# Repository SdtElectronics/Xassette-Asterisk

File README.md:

# Xassette-Asterisk
Evaluation board for AllWinner's RISC-V 64 SoC F133/D1s

## Highlights
* Breaks out all IOs, involving analog peripherals, in a compact 56*56mm 2-layer board
* Comes with standard interfaces including USB, micro SD, LCD, Line-in and headphone
* Optimized components arrangement for soldering on a hot plate

## About the Chip
D1s/F133: RISC-V 64 single core @1.008G with in package 64MB DDR2

## Guides
[Quick Start](docs/quickStart.md)

[Troubleshooting](docs/troubleshooting.md)

[Wi-Fi](docs/WiFi.md)

## Pin Out

Pins for LCD and DVP camera can also be used as IOs. See schematic below for detailed pin assignment.

## Schematic & BOM

The schematic in KiCAD format is available under [hw](hw/). BOM in csv format is at [docs/BOM.csv](docs/BOM.csv), and kitspace provides an [online BOM](https://kitspace.org/interactive_bom/?github.com/SdtElectronics/Xassette-Asterisk). Do note that many components are optional (required by some specific peripherals)!

## Notes
* Leave all BOOT selection resistors unconnected if only one BOOT media is present
* Choose load capacitors according to specs of crystals
* When board is to be powered by 3.3V, connect to the power via the 3.3V pin of the pinheader, and `D4` should be soldered. Note USB host will not work properly in this condition due to the absence of 5V power.

## Accessories
### IO Expansion Board
To make use of IOs in the LCD port easier, [this expansion board](hw/auxiliary/Brk40p) converts all nets from FPC to 2.54mm pin headers with labeled IO indices. For 24pin DVP port, there is also an [expansion board](https://github.com/SdtElectronics/Biscuits/tree/master/24P_FPC_FFC_Breakout) but with no labels.

## CHANGELOG
### hw-v0.2 
* Added WiFi Module on `sdc2`, sharing pins with SPI Flash
* Added FEL button
* Added ESD protection on USB and audio jacks
* Changed pin headers of TVIN and FMIN (`J10`) to 2x3 2.00mm to optimize routing of USB

### fw-v0.2
* Enabled pins of `sdc2` for SDIO
* Packed driver for RTL8189ftv WiFi module

**NOTE**: hw-v0.1 board can **NOT** boot fw-v0.2 firmware. Use fw-v0.1 instead.

### hw-v0.3
* Fix pull-up/down resistors for USB-PD role detection
* Align voltage of `VDDIO` in DVP interface with `VCC-PE`

## FAQ
> Are you going to sell some manufactured boards?

No. I have no time and resource to batch manufacture this board. Some commercial boards should come in a couple of months (not from me).

> Where to buy some D1s chips?

There are several suppliers providing samples on taobao.

> Where to find the BSP? Can I build the firmware myself?

The tina BSP for D1s is opened to public and you can download it via [the mirror at linux-sunxi.org](https://dl.linux-sunxi.org/D1/SDK/). There is also [a good guide on linux-sunxi.org](https://linux-sunxi.org/D1_SDK_Howto) covering the building and trouble shooting.

> More information? Like what can this board do now?

The progress of this project is logged at [this Hackaday page](https://hackaday.io/project/182389-the-cheapest-risc-v-64-computer-by-now), and this repository will contain the source and documentation of this board only. Currently this board can boot up the tina Linux system (an OpenWRT fork by Allwinner) and populate a shell prompt via the serial, drive a parallel RGB display, play sounds via the headphone socket, and record audio from MIC. More functionalities will be tested in the future.

**Additional Words**

This project has gained unexpected popularity since the announcement. Thanks for all the interest! However, I am merely an enthusiast with limited time can be put on this, so I am sorry to disappoint who want to buy one. It is perfectly Okay if someone want to put this into production, as long as my work is acknowledged and the Licence is followed (better if you could contact me in advance). 

D1s is an awesome chip with many features to be exploited. Designing a PCB is not hard as the arrangement of pins is quite thoughtful. The crucial part is correct values of some key components, and they were all marked in the schematic. A symbol of D1s with annotated pins is also included in this repository, so this should also be a good start point for your own design.

## External Links
[Page on Hackaday ](https://hackaday.io/project/182389-the-cheapest-risc-v-64-computer-by-now)

[Post about batch manufacturing by cnx-software](https://www.cnx-software.com/2021/12/24/manufacturing-xassette-asterisk-open-source-hardware-board/)

[WiKi on Linux-sunxi.org](https://linux-sunxi.org/Xassette_Asterisk)

## Licence
This project is available under the [CERN OHL-w v2](https://ohwr.org/project/cernohl/wikis/Documents/CERN-OHL-version-2) licence.

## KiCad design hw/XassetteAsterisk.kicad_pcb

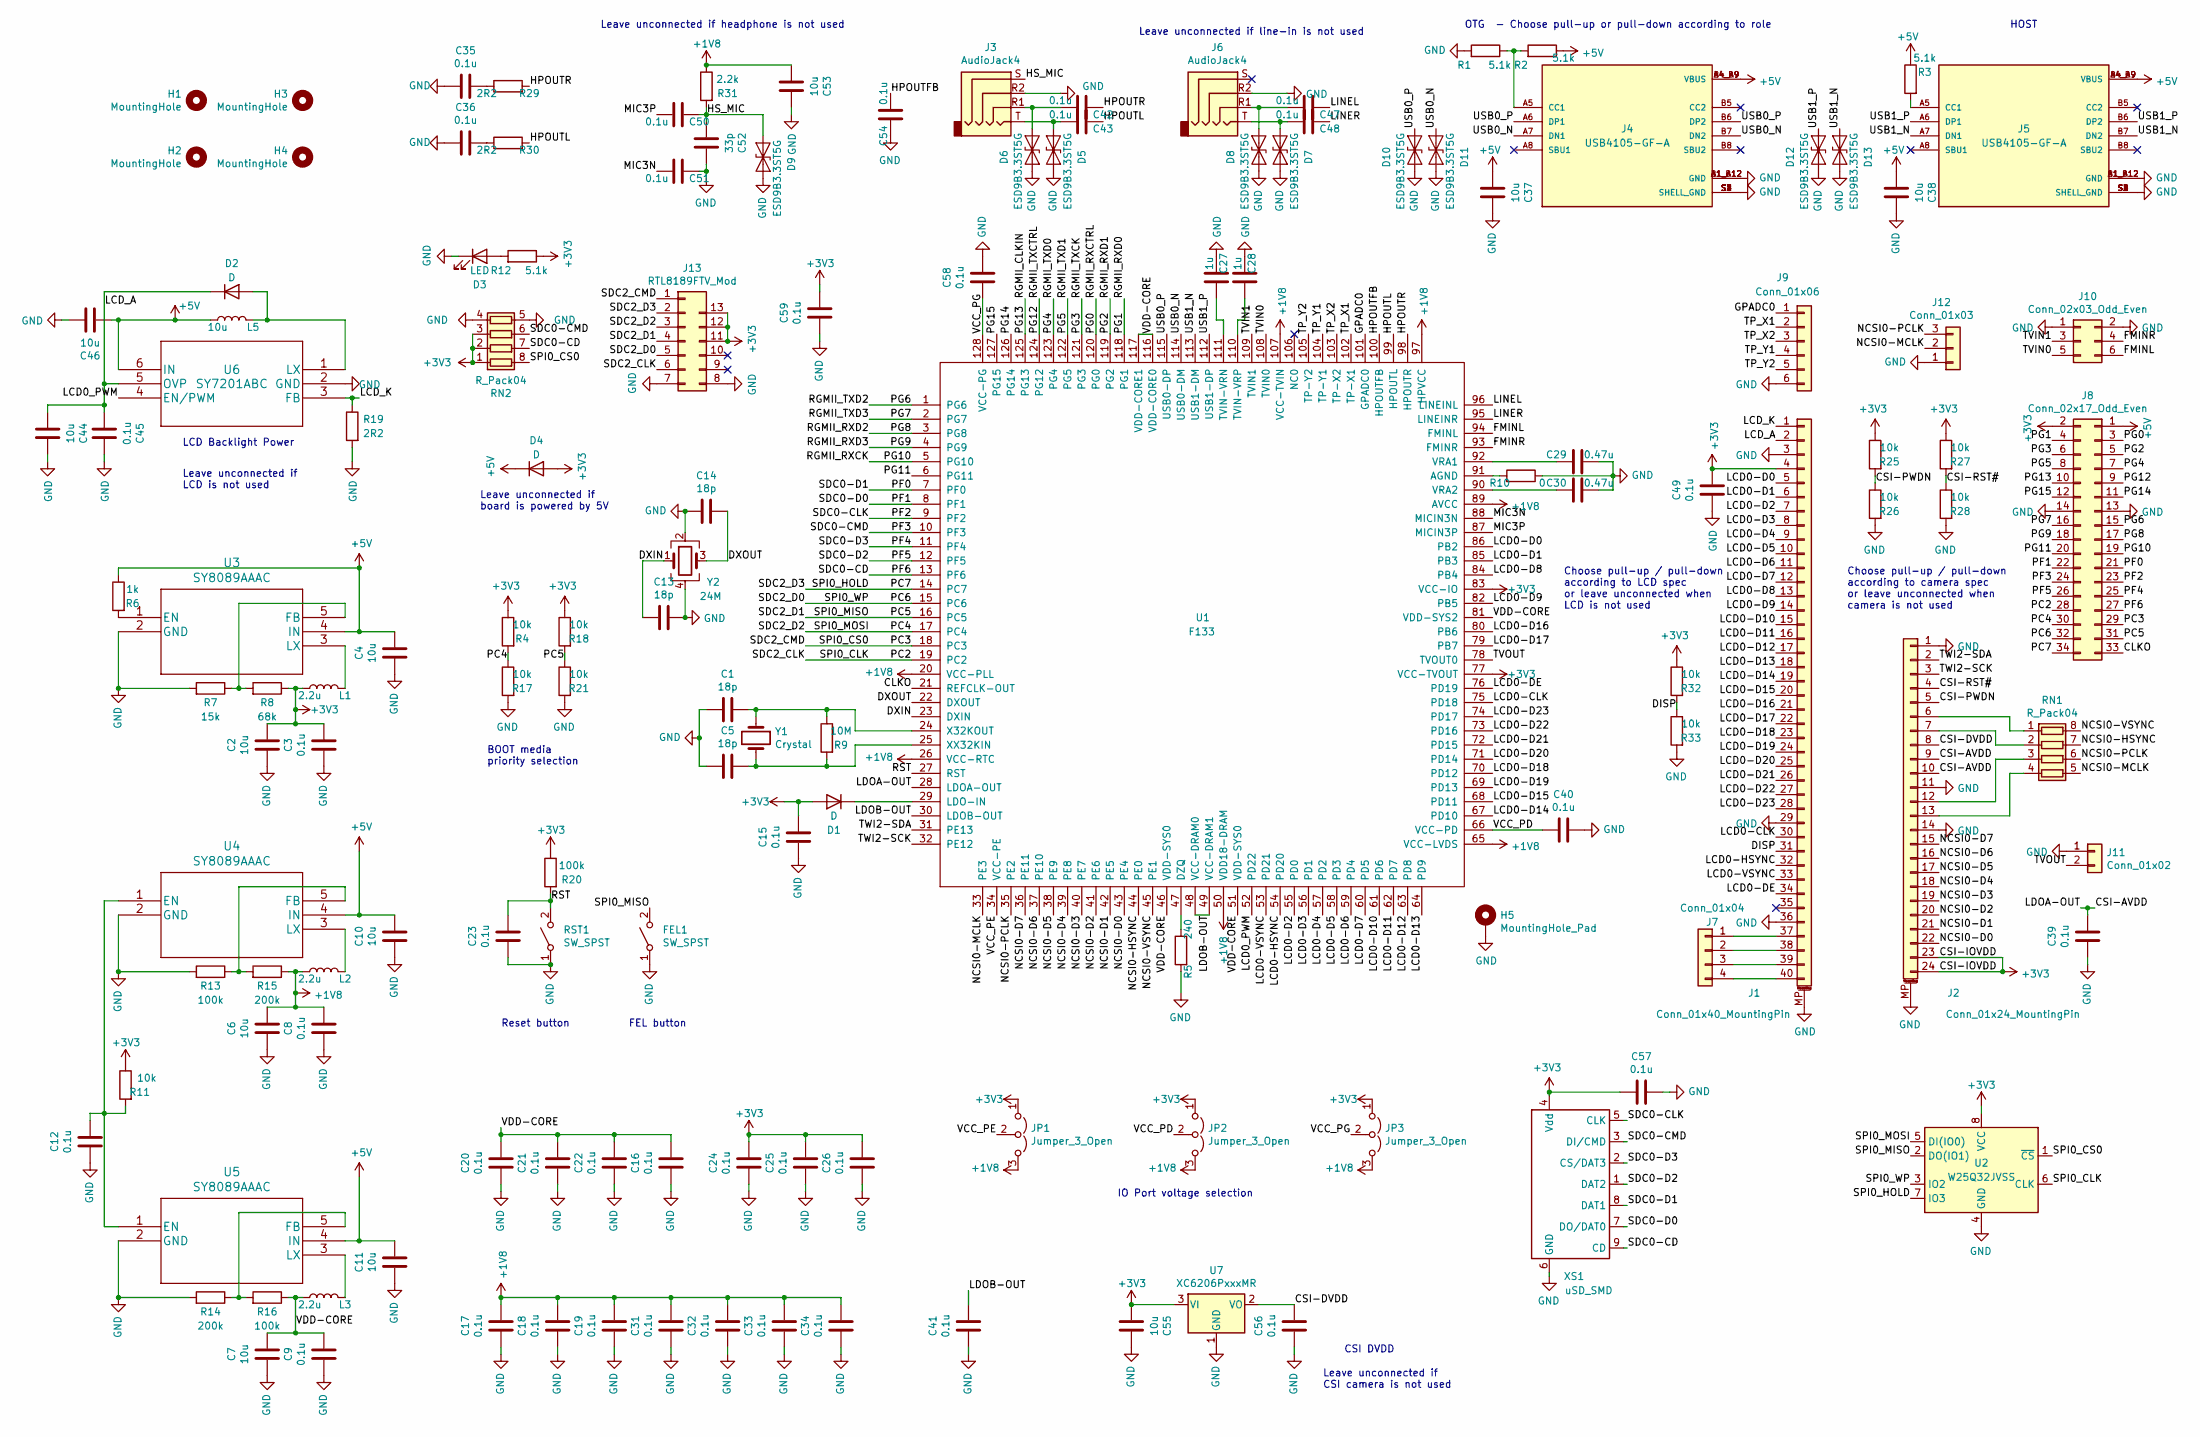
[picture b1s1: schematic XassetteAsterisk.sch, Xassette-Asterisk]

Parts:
C1, C5, C13, C14: 18p; C_0603_1608Metric
C2, C4, C6, C7, C10, C11, C37, C38, C44, C46, C53, C55: 10u; C_0603_1608Metric
C3, C8, C9, C12, C15, C16, C17, C18, C19, C20, C21, C22, C23, C24, C25, C26, C31, C32, C33, C34, C35, C36, C39, C40, C41, C42, C43, C45, C47, C48, C49, C50, C51, C54, C56, C57, C58, C59: 0.1u; C_0603_1608Metric
C27, C28: 1u; C_0603_1608Metric
C29, C30: 0.47u; C_0603_1608Metric
C52: 33p; C_0603_1608Metric
D1, D2, D4: D; D_SOD-323
D3: LED; LED_0603_1608Metric
D5, D6, D7, D8, D9, D10, D11, D12, D13: ESD9B3.3ST5G; D_SOD-923
FEL1: SW_SPST; SW_SPST_EVQPE1
H1, H2, H3, H4: MountingHole; MountingHole_3.2mm_M3
H5: MountingHole_Pad; SolderWirePad_1x01_SMD_5x10mm
J1: Conn_01x40_MountingPin; TE_4-1734839-0_1x40-1MP_P0.5mm_Horizontal
J2: Conn_01x24_MountingPin; TE_2-1734839-4_1x24-1MP_P0.5mm_Horizontal
J3, J6: AudioJack4; Jack_3.5mm_PJ320D_Horizontal
J4, J5: USB4105-GF-A; GCT_USB4105-GF-A; PARTREV A3
J7: Conn_01x04; PinSocket_1x04_P2.00mm_Vertical
J8: Conn_02x17_Odd_Even; PinSocket_2x17_P2.54mm_Vertical
J9: Conn_01x06; PinHeader_1x06_P2.00mm_Vertical
J10: Conn_02x03_Odd_Even; PinHeader_2x03_P2.00mm_Vertical
J11: Conn_01x02; PinHeader_1x02_P2.00mm_Vertical
J12: Conn_01x03; PinHeader_1x03_P2.54mm_Vertical
J13: RTL8189FTV_Mod; 8189Mod
JP1, JP2, JP3: Jumper_3_Open; SolderJumper-3_P2.0mm_Open_TrianglePad1.0x1.5mm
L1, L2, L3: 2.2u; L_Wuerth_MAPI-2510
L5: 10u; L_Wuerth_MAPI-2510
R1, R2, R3, R12: 5.1k; R_0603_1608Metric
R4, R11, R17, R18, R21, R25, R26, R27, R28, R32, R33: 10k; R_0603_1608Metric
R5: 240; R_0603_1608Metric
R6: 1k; R_0603_1608Metric
R7: 15k; R_0603_1608Metric
R8: 68k; R_0603_1608Metric
R9: 10M; R_0603_1608Metric
R10: 0; R_0603_1608Metric
R13, R16, R20: 100k; R_0603_1608Metric
R14, R15: 200k; R_0603_1608Metric
R19, R29, R30: 2R2; R_0603_1608Metric
R31: 2.2k; R_0603_1608Metric
RN1, RN2: R_Pack04; R_Array_Convex_4x0603
RST1: SW_SPST; SW_SPST_EVQPE1
U1: F133; LQFP-128_14x14mm_P0.4mm
U2: W25Q32JVSS; SOIC-8_5.23x5.23mm_P1.27mm
U3, U4, U5: SY8089AAAC; SOT-23-5
U6: SY7201ABC; SOT-23-6
U7: XC6206PxxxMR; SOT-23
XS1: uSD_SMD; Conn_uSDcard
Y1: Crystal; Crystal_SMD_3215-2Pin_3.2x1.5mm
Y2: 24M; Crystal_SMD_3225-4Pin_3.2x2.5mm

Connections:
+1V8: C6.1, C8.1, C17.1, C18.1, C19.1, C31.1, C32.1, C33.1, C34.1, C53.1, JP1.3 (B), JP2.3 (B), JP3.3 (B), L2.1, R15.1, R31.1, U1.20 (VCC-PLL), U1.26 (VCC-RTC), U1.50 (VDD18-DRAM), U1.65 (VCC-LVDS), U1.89 (AVCC), U1.97 (HPVCC), U1.107 (VCC-TVIN)
+3V3: C2.1, C3.1, C15.1, C24.1, C25.1, C26.1, C49.1, C55.1, C57.1, C59.1, D1.2 (A), D4.2 (A), J1.4, J2.23, J2.24, J8.2, J13.11, J13.12, J13.13, JP1.1 (A), JP2.1 (A), JP3.1 (A), L1.1, R4.1, R8.1, R11.1, R12.1, R18.1, R20.1, R25.1, R27.1, R32.1, RN2.1 (R1.1), RN2.2 (R2.1), RN2.3 (R3.1), U1.77 (VCC-TVOUT), U1.83 (VCC-IO), U2.8 (VCC), U7.3 (VI), XS1.4 (Vdd)
+5V: C4.1, C10.1, C11.1, C37.1, C38.1, C46.1, D4.1 (K), J4.A4_B9 (VBUS), J4.B4_A9 (VBUS), J5.A4_B9 (VBUS), J5.B4_A9 (VBUS), J8.1, L5.1, R2.1, R3.1, R6.1, U3.4 (IN), U4.4 (IN), U5.4 (IN), U6.6 (IN)
/CLKO: J8.33, U1.21 (REFCLK-OUT)
/CSI-AVDD: C39.1, J2.9, J2.10, U1.28 (LDOA-OUT)
/CSI-DVDD: C56.1, J2.8, U7.2 (VO)
/CSI-PWDN: J2.5, R25.2, R26.1
/CSI-RST#: J2.4, R27.2, R28.1
/DISP: J1.31, R32.2, R33.1
/DXIN: C13.2, U1.23 (DXIN), Y2.1
/DXOUT: C14.1, U1.22 (DXOUT), Y2.3
/FMINL: J10.6, U1.94 (FMINL)
/FMINR: J10.4, U1.93 (FMINR)
/GPADC0: J9.1, U1.101 (GPADC0)
/HPOUTFB: C54.1, U1.100 (HPOUTFB)
/HPOUTL: C43.2, R30.2, U1.99 (HPOUTL)
/HPOUTR: C42.2, R29.2, U1.98 (HPOUTR)
/HS_MIC: C50.2, C52.1, D9.2 (A2), J3.S, R31.2
/LCD0-CLK: J1.30, U1.75 (PD18)
/LCD0-D0: J1.5, U1.86 (PB2)
/LCD0-D1: J1.6, U1.85 (PB3)
/LCD0-D2: J1.7, U1.55 (PD0)
/LCD0-D3: J1.8, U1.56 (PD1)
/LCD0-D4: J1.9, U1.57 (PD2)
/LCD0-D5: J1.10, U1.58 (PD3)
/LCD0-D6: J1.11, U1.59 (PD4)
/LCD0-D7: J1.12, U1.60 (PD5)
/LCD0-D8: J1.13, U1.84 (PB4)
/LCD0-D9: J1.14, U1.82 (PB5)
/LCD0-D10: J1.15, U1.61 (PD6)
/LCD0-D11: J1.16, U1.62 (PD7)
/LCD0-D12: J1.17, U1.63 (PD8)
/LCD0-D13: J1.18, U1.64 (PD9)
/LCD0-D14: J1.19, U1.67 (PD10)
/LCD0-D15: J1.20, U1.68 (PD11)
/LCD0-D16: J1.21, U1.80 (PB6)
/LCD0-D17: J1.22, U1.79 (PB7)
/LCD0-D18: J1.23, U1.70 (PD12)
/LCD0-D19: J1.24, U1.69 (PD13)
/LCD0-D20: J1.25, U1.71 (PD14)
/LCD0-D21: J1.26, U1.72 (PD15)
/LCD0-D22: J1.27, U1.73 (PD16)
/LCD0-D23: J1.28, U1.74 (PD17)
/LCD0-DE: J1.34, U1.76 (PD19)
/LCD0-HSYNC: J1.32, U1.54 (PD20)
/LCD0-VSYNC: J1.33, U1.53 (PD21)
/LCD0_PWM: U1.52 (PD22), U6.4 (EN/PWM)
/LCD_A: C44.1, C45.1, D2.1 (K), J1.2, U6.5 (OVP)
/LCD_K: J1.1, R19.1, U6.3 (FB)
/LDOB-OUT: C41.1, U1.30 (LDOB-OUT), U1.48 (VCC-DRAM0), U1.49 (VCC-DRAM1)
/LINEL: C47.2, U1.96 (LINEINL)
/LINER: C48.2, U1.95 (LINEINR)
/MIC3N: C51.1, U1.88 (MICIN3N)
/MIC3P: C50.1, U1.87 (MICIN3P)
/NCSI0-D0: J2.22, U1.43 (PE4)
/NCSI0-D1: J2.21, U1.42 (PE5)
/NCSI0-D2: J2.20, U1.41 (PE6)
/NCSI0-D3: J2.19, U1.40 (PE7)
/NCSI0-D4: J2.18, U1.39 (PE8)
/NCSI0-D5: J2.17, U1.38 (PE9)
/NCSI0-D6: J2.16, U1.37 (PE10)
/NCSI0-D7: J2.15, U1.36 (PE11)
/NCSI0-HSYNC: RN1.7 (R2.2), U1.44 (PE0)
/NCSI0-MCLK: J12.2, RN1.5 (R4.2), U1.33 (PE3)
/NCSI0-PCLK: J12.3, RN1.6 (R3.2), U1.35 (PE2)
/NCSI0-VSYNC: RN1.8 (R1.2), U1.45 (PE1)
/PC2: J8.28, J13.6, U1.19 (PC2), U2.6 (CLK)
/PC3: J8.29, J13.1, RN2.8 (R1.2), U1.18 (PC3), U2.1 (~CS)
/PC4: J8.30, J13.3, R4.2, R17.1, U1.17 (PC4), U2.5 (DI(IO0))
/PC5: FEL1.2 (B), J8.31, J13.4, R18.2, R21.1, U1.16 (PC5), U2.2 (DO(IO1)); also elsewhere on the board
/PC6: J8.32, J13.5, U1.15 (PC6), U2.3 (IO2)
/PC7: J8.34, J13.2, U1.14 (PC7), U2.7 (IO3)
/PF0: J8.21, U1.7 (PF0), XS1.8 (DAT1)
/PF1: J8.22, U1.8 (PF1), XS1.7 (DO/DAT0)
/PF2: J8.23, U1.9 (PF2), XS1.5 (CLK)
/PF3: J8.24, RN2.6 (R3.2), U1.10 (PF3), XS1.3 (DI/CMD)
/PF4: J8.25, U1.11 (PF4), XS1.2 (CS/DAT3)
/PF5: J8.26, U1.12 (PF5), XS1.1 (DAT2)
/PF6: J8.27, RN2.7 (R2.2), U1.13 (PF6), XS1.9 (CD)
/PG0: J8.3, U1.120 (PG0)
/PG1: J8.4, U1.118 (PG1)
/PG2: J8.5, U1.119 (PG2)
/PG3: J8.6, U1.121 (PG3)
/PG4: J8.7, U1.123 (PG4)
/PG5: J8.8, U1.122 (PG5)
/PG6: J8.15, U1.1 (PG6)
/PG7: J8.16, U1.2 (PG7)
/PG8: J8.17, U1.3 (PG8)
/PG9: J8.18, U1.4 (PG9)
/PG10: J8.19, U1.5 (PG10)
/PG11: J8.20, U1.6 (PG11)
/PG12: J8.9, U1.124 (PG12)
/PG13: J8.10, U1.125 (PG13)
/PG14: J8.11, U1.126 (PG14)
/PG15: J8.12, U1.127 (PG15)
/RST: C23.1, R20.2, RST1.2 (B), U1.27 (RST); also elsewhere on the board
/TP_X1: J9.2, U1.102 (TP-X1)
/TP_X2: J9.3, U1.103 (TP-X2)
/TP_Y1: J9.4, U1.104 (TP-Y1)
/TP_Y2: J9.5, U1.105 (TP-Y2)
/TVIN0: J10.5, U1.108 (TVIN0)
/TVIN1: J10.3, U1.109 (TVIN1)
/TVOUT: J11.2, U1.78 (TVOUT0)
/TWI2-SCK: J2.3, U1.32 (PE12)
/TWI2-SDA: J2.2, U1.31 (PE13)
/USB0_N: D11.2 (A2), J4.A7 (DN1), J4.B7 (DN2), U1.114 (USB0-DM)
/USB0_P: D10.2 (A2), J4.A6 (DP1), J4.B6 (DP2), U1.115 (USB0-DP)
/USB1_N: D13.2 (A2), J5.A7 (DN1), J5.B7 (DN2), U1.113 (USB1-DM)
/USB1_P: D12.2 (A2), J5.A6 (DP1), J5.B6 (DP2), U1.112 (USB1-DP)
/VCC_PD: C40.2, JP2.2 (C), U1.66 (VCC-PD)
/VCC_PE: JP1.2 (C), U1.34 (VCC-PE)
/VCC_PG: C58.2, JP3.2 (C), U1.128 (VCC-PG)
/VDD-CORE: C7.1, C9.1, C16.1, C20.1, C21.1, C22.1, L3.1, R16.1, U1.46 (VDD-SYS0), U1.51 (VDD-SYS0), U1.81 (VDD-SYS2), U1.116 (VDD-CORE0), U1.117 (VDD-CORE1)
GND: C1.2, C2.2, C3.2, C4.2, C5.2, C6.2, C7.2, C8.2, C9.2, C10.2, C11.2, C12.2, C13.1, C14.2, C15.2, C16.2, C17.2, C18.2, C19.2, C20.2, C21.2, C22.2, C23.2, C24.2, C25.2, C26.2, C27.2, C28.2, C29.1, C30.1, C31.2, C32.2, C33.2, C34.2, C35.1, C36.1, C37.2, C38.2, C39.2, C40.1, C41.2, C44.2, C45.2, C46.2, C49.2, C51.2, C52.2, C53.2, C54.2, C55.2, C56.2, C57.2, C58.1, C59.2, D3.1 (K), D5.1 (A1), D6.1 (A1), D7.1 (A1), D8.1 (A1), D9.1 (A1), D10.1 (A1), D11.1 (A1), D12.1 (A1), D13.1 (A1), FEL1.1 (A), H5.1, J1.3, J1.29, J1.36, J1.MP (MountPin), J2.1, J2.11, J2.14, J2.MP (MountPin), J3.R2, J4.A1_B12 (GND), J4.B1_A12 (GND), J4.S1 (SHELL_GND), J4.S2 (SHELL_GND), J4.S3 (SHELL_GND), J4.S4 (SHELL_GND), J5.A1_B12 (GND), J5.B1_A12 (GND), J5.S1 (SHELL_GND), J5.S2 (SHELL_GND), J5.S3 (SHELL_GND), J5.S4 (SHELL_GND), J6.R2, J8.13, J8.14, J9.6, J10.1, J10.2, J11.1, J12.1, J13.7, J13.8, R1.2, R5.2, R7.2, R10.1, R13.2, R14.2, R17.2, R19.2, R21.2, R26.2, R28.2, R33.2, RN2.4 (R4.1), RN2.5 (R4.2), RST1.1 (A), U2.4 (GND), U3.2 (GND), U4.2 (GND), U5.2 (GND), U6.2 (GND), U7.1 (GND), XS1.6 (GND), Y2.2, Y2.4; also elsewhere on the board
unnamed: C1.1, R9.1, U1.24 (X32KOUT), Y1.1
unnamed: C5.1, R9.2, U1.25 (XX32KIN), Y1.2
unnamed: C12.1, R11.2, U4.1 (EN), U5.1 (EN)
unnamed: C27.1, U1.111 (TVIN-VRN)
unnamed: C28.1, U1.110 (TVIN-VRP)
unnamed: C29.2, U1.92 (VRA1)
unnamed: C30.2, U1.90 (VRA2)
unnamed: C35.2, R29.1
unnamed: C36.2, R30.1
unnamed: C42.1, D6.2 (A2), J3.R1
unnamed: C43.1, D5.2 (A2), J3.T
unnamed: C47.1, D8.2 (A2), J6.R1
unnamed: C48.1, D7.2 (A2), J6.T
unnamed: D1.1 (K), U1.29 (LDO-IN)
unnamed: D2.2 (A), L5.2, U6.1 (LX)
unnamed: D3.2 (A), R12.2
unnamed: J1.37, J7.1
unnamed: J1.38, J7.2
unnamed: J1.39, J7.3
unnamed: J1.40, J7.4
unnamed: J2.6, RN1.1 (R1.1)
unnamed: J2.7, RN1.2 (R2.1)
unnamed: J2.12, RN1.3 (R3.1)
unnamed: J2.13, RN1.4 (R4.1)
unnamed: J4.A5 (CC1), R1.1, R2.2
unnamed: J5.A5 (CC1), R3.2
unnamed: L1.2, U3.3 (LX)
unnamed: L2.2, U4.3 (LX)
unnamed: L3.2, U5.3 (LX)
unnamed: R5.1, U1.47 (DZQ)
unnamed: R6.2, U3.1 (EN)
unnamed: R7.1, R8.2, U3.5 (FB)
unnamed: R10.2, U1.91 (AGND)
unnamed: R13.1, R15.2, U4.5 (FB)
unnamed: R14.1, R16.2, U5.5 (FB)

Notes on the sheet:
Leave unconnected if board is powered by 5V
Leave unconnected if LCD is not used
LCD Backlight Power
BOOT media priority selection
IO Port voltage selection
Leave unconnected if CSI camera is not used
CSI DVDD
Choose pull-up / pull-down according to camera spec or leave unconnected when camera is not used
Choose pull-up / pull-down according to LCD spec or leave unconnected when LCD is not used
Leave unconnected if headphone is not used
Leave unconnected if line-in is not used
OTG - Choose pull-up or pull-down according to role
Reset button
HOST
FEL button

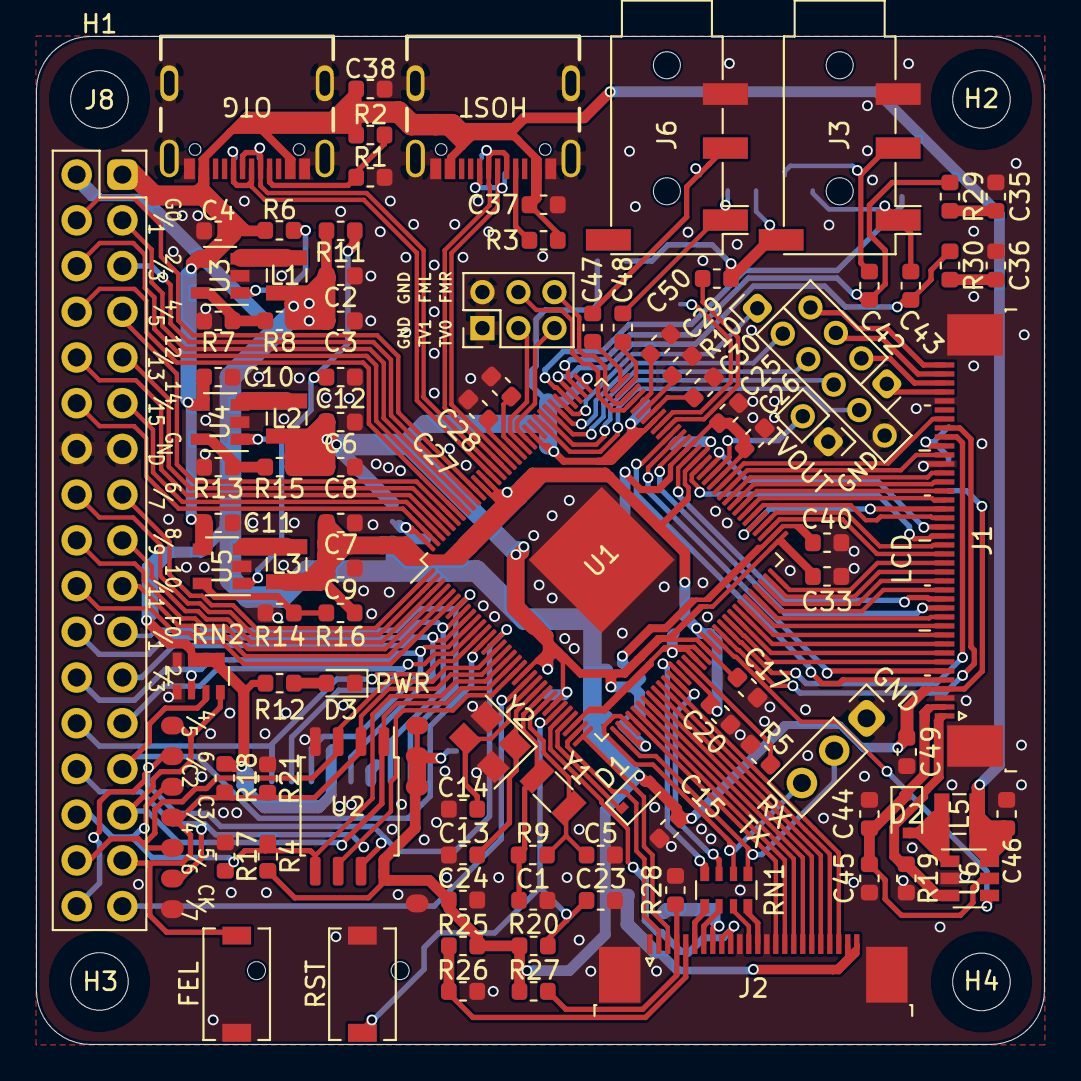
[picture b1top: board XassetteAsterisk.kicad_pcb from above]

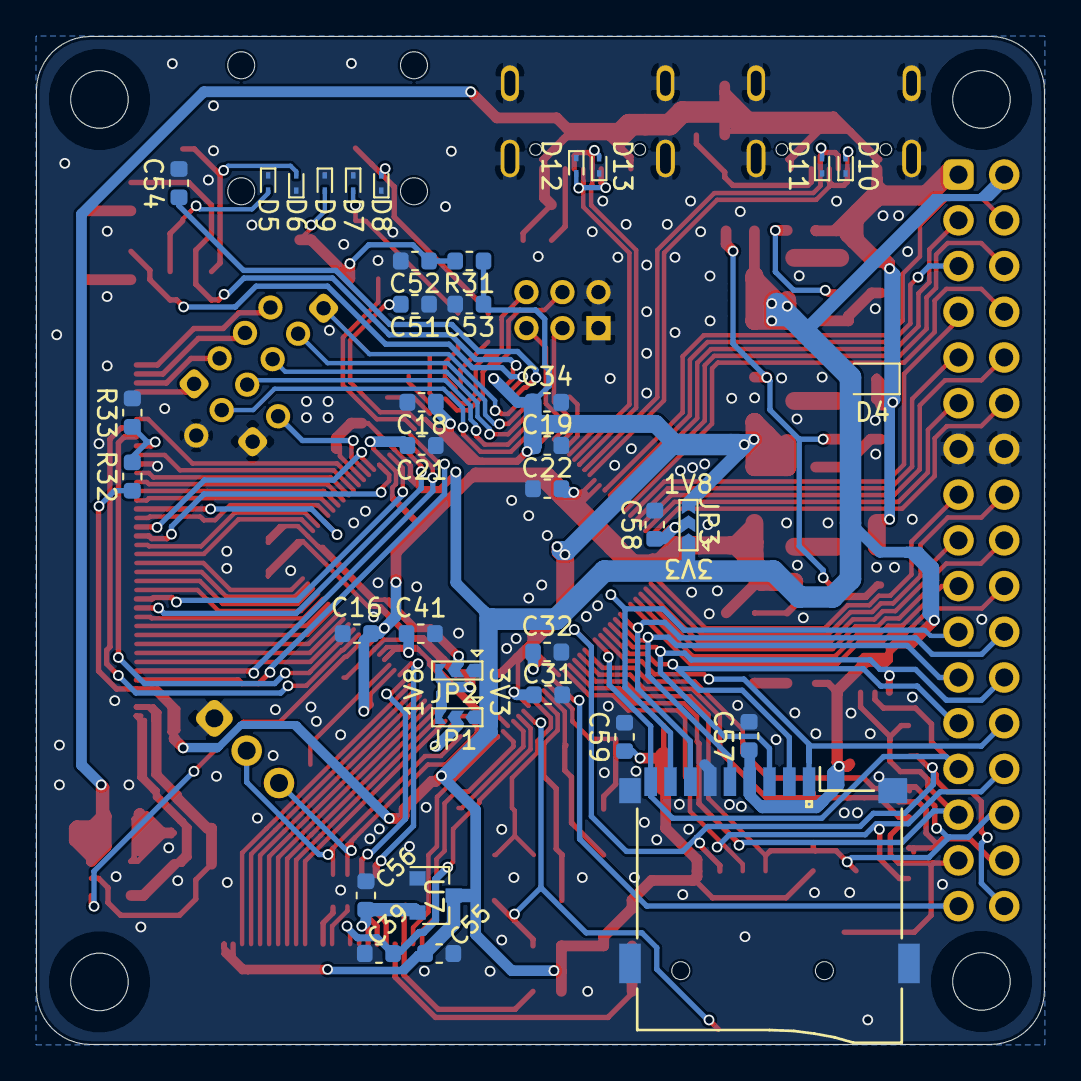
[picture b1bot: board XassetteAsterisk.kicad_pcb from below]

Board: 2 copper layers, 56.0 x 56.0 mm, 142 parts (38 on the bottom side), 149 nets.

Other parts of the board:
FEL: SW_SPST; SW_SPST_EVQPE1
RST: SW_SPST; SW_SPST_EVQPE1
Ref**: Val**; rvlogo_inv

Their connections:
/PC5: FEL.2; also elsewhere on the board
/RST: RST.2; also elsewhere on the board
GND: FEL.1, RST.1; also elsewhere on the board

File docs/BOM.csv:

Comment,Designator,Footprint,Pins,Quantity
1u,"C28,C27,",C_0603_1608Metric,2,2
0.47u,"C29,C30,",C_0603_1608Metric,2,2
10u,"C44,C38,C37,C4,C2,C6,C7,C10,C11,",C_0603_1608Metric,2,9
0.1u,"C50,C49,C48,C47,C46,C45,C43,C42,C40,C36,C35,C33,C17,C26,C25,C24,C1,C5,C23,C20,C3,C12,C9,C8,C15,",C_0603_1608Metric,2,27
1N5819,"D1,D2,",D_SOD-323,2,2
LED,"D3,",LED_0603_1608Metric,2,1
Conn_01x40_MountingPin,"J1,",TE_4-1734839-0_1x40-1MP_P0.5mm_Horizontal,42,1
Conn_01x24_MountingPin,"J2,",TE_2-1734839-4_1x24-1MP_P0.5mm_Horizontal,26,1
2.2u,"L2,L3,L1,",L_Wuerth_MAPI-2510,2,3
10u,"L5,",L_Wuerth_MAPI-2510,2,1
0,"R10,",R_0603_1608Metric,2,1
100k,"R13,R11,R12,R16,",R_0603_1608Metric,2,4
200k,"R15,R14,",R_0603_1608Metric,2,2
1.5k,"R24,R3,R1,",R_0603_1608Metric,2,4
2R2,"R30,R29,R19,",R_0603_1608Metric,2,3
10k,"R34,R23,R22,",R_0603_1608Metric,2,11
240,"R5,",R_0603_1608Metric,2,1
15k,"R7,",R_0603_1608Metric,2,1
68k,"R8,",R_0603_1608Metric,2,1
1k,"R6,R20,",R_0603_1608Metric,2,3
0,"RN1,",R_Array_Convex_4x0603,8,1
SW_SPST,"RST,",SW_SPST_FSMSM,2,1
F133,"U1,",LQFP-128_14x14mm_P0.4mm,128,1
W25Q32JVSS,"U2,",SOIC-8_5.23x5.23mm_P1.27mm,8,1
SY8089AAAC,"U4,U3,U5,",SOT-23-5,5,3
SY7201ABC,"U6,",SOT-23-6,6,1
32.768k,"Y1,",Crystal_SMD_3215-2Pin_3.2x1.5mm,2,1
24M,"Y2,",Crystal_SMD_3225-4Pin_3.2x2.5mm,4,1
33p,"C52,",C_0603_1608Metric,2,1
10u,"C53,",C_0603_1608Metric,2,2
0.1u,"C58,C57,C54,C51,C41,C39,C34,C32,C31,C19,C18,C16,C21,C22,",C_0603_1608Metric,2,15
2.2k,"R31,",R_0603_1608Metric,2,1
10k,"R32,",R_0603_1608Metric,2,2
Through Hole Items ,,,,
Conn_02x03_Odd_Even,"J10,",PinHeader_2x03_P2.54mm_Vertical,6,1
Conn_01x02,"J11,",PinHeader_1x02_P2.00mm_Vertical,2,1
Conn_01x03,"J12,",PinHeader_1x03_P2.54mm_Vertical,3,1
PJ320D,"J3,J6,",Jack_3.5mm_PJ320D_Horizontal,6,2
USB4105-GF-A,"J5,J4,",GCT_USB4105-GF-A,18,2
Conn_01x04,"J7,",PinSocket_1x04_P2.00mm_Vertical,4,1
Conn_02x17_Odd_Even,"J8,",PinSocket_2x17_P2.54mm_Vertical,34,1
Conn_01x06,"J9,",PinHeader_1x06_P2.00mm_Vertical,6,1
uSD_SMD,"XS1,",Conn_uSDcard,15,1

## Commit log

2021-10-27 schematic revision
2021-10-29 update README with schematic
2021-11-05 add BOM list
2021-11-07 minor changes in schematic
2021-11-15 add expansion board
2021-11-21 add pinout to README
2021-11-24 Add kitspace.yaml
2021-11-25 add guides
2021-12-09 hw upgrade to v0.2
2021-12-13 add documentation for WiFi
2021-12-13 hw upgrade to v0.3
2021-12-30 add external links in README
